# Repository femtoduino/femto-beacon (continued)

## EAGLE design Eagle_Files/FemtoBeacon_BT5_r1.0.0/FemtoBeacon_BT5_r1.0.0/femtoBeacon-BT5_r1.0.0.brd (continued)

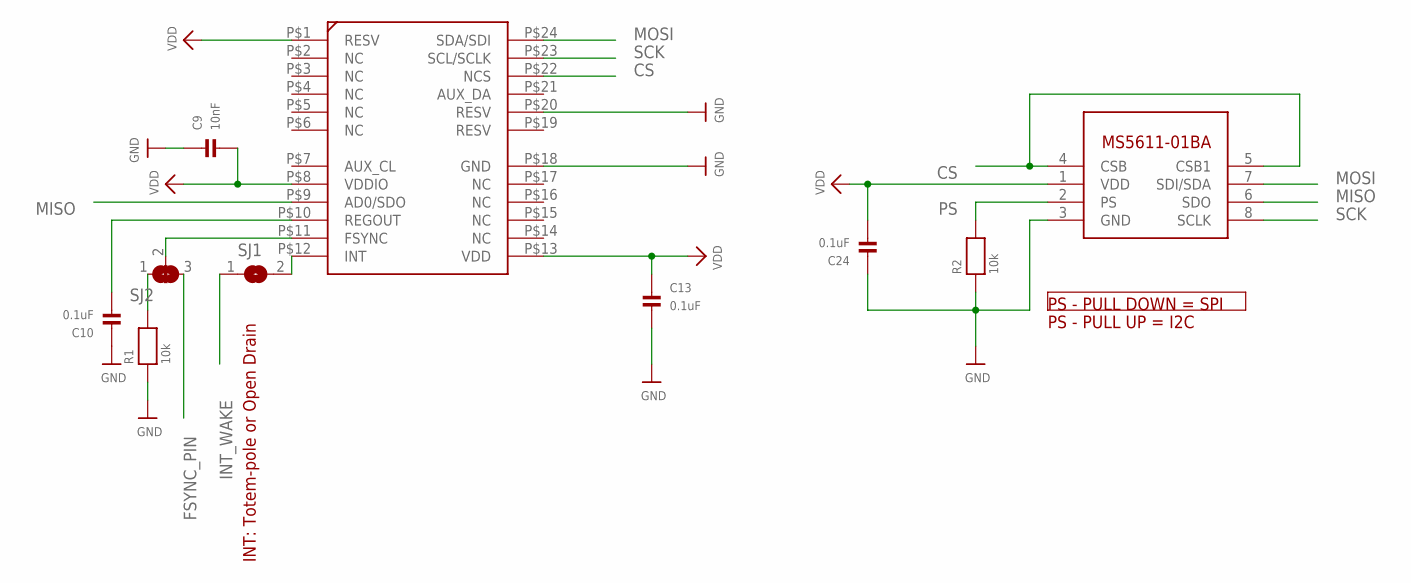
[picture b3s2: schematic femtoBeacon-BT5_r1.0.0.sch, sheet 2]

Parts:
BARO: MS5611-01BA03
C9: 10nF; _0402MP
C10, C13, C24: 0.1uF; _0402MP
IMU: MPU-9250; QFN_3X3MM
R1, R2: 10k; _0402MP
SJ1: SOLDERJUMPERCLOSED; SOLDERJUMPER_CLOSEDWIRE
SJ2: SOLDERJUMPER_2WAY; SOLDERJUMPER_2WAY_OPEN_NOPASTE

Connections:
CS: BARO.4 (CSB), BARO.5 (CSB1), IMU.P$22 (NCS); also elsewhere on the board
FSYNC: IMU.P$11 (FSYNC), SJ2.2
FSYNC_PIN: SJ2.3; also elsewhere on the board
GND: BARO.3 (GND), C9.1, C10.1, C13.2, C24.1, IMU.P$18 (GND), IMU.P$20 (RESV), R1.1, R2.1; also elsewhere on the board
INT: IMU.P$12 (INT), SJ1.2
INT_WAKE: SJ1.1; also elsewhere on the board
MISO: BARO.6 (SDO), IMU.P$9 (AD0/SDO); also elsewhere on the board
MOSI: BARO.7 (SDI/SDA), IMU.P$24 (SDA/SDI); also elsewhere on the board
unnamed: R1.2, SJ2.1
unnamed: C10.2, IMU.P$10 (REGOUT)
PS: BARO.2 (PS), R2.2
SCK: BARO.8 (SCLK), IMU.P$23 (SCL/SCLK); also elsewhere on the board
VDD: BARO.1 (VDD), C9.2, C13.1, C24.2, IMU.P$1 (RESV), IMU.P$8 (VDDIO), IMU.P$13 (VDD); also elsewhere on the board

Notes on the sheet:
INT: Totem-pole or Open Drain
PS - PULL DOWN = SPI
PS - PULL UP = I2C

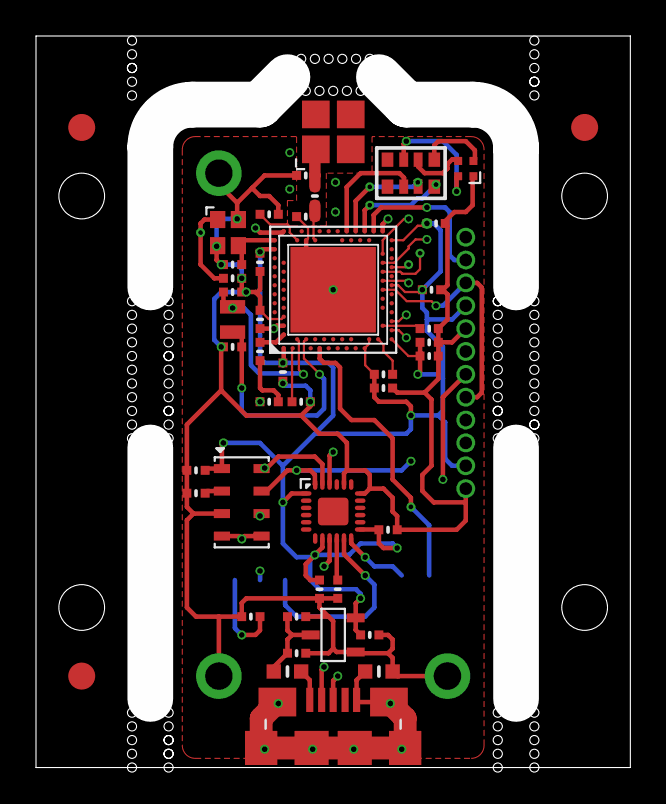
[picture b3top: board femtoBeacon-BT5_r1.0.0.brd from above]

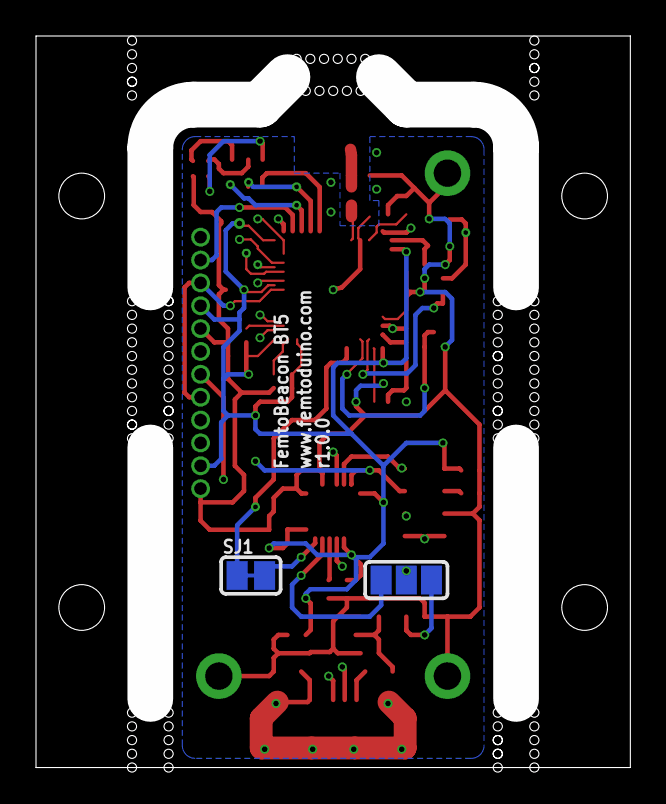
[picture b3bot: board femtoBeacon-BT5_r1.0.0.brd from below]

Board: 4 copper layers, 33.0 x 40.6 mm, 49 parts (2 on the bottom side), 40 nets.

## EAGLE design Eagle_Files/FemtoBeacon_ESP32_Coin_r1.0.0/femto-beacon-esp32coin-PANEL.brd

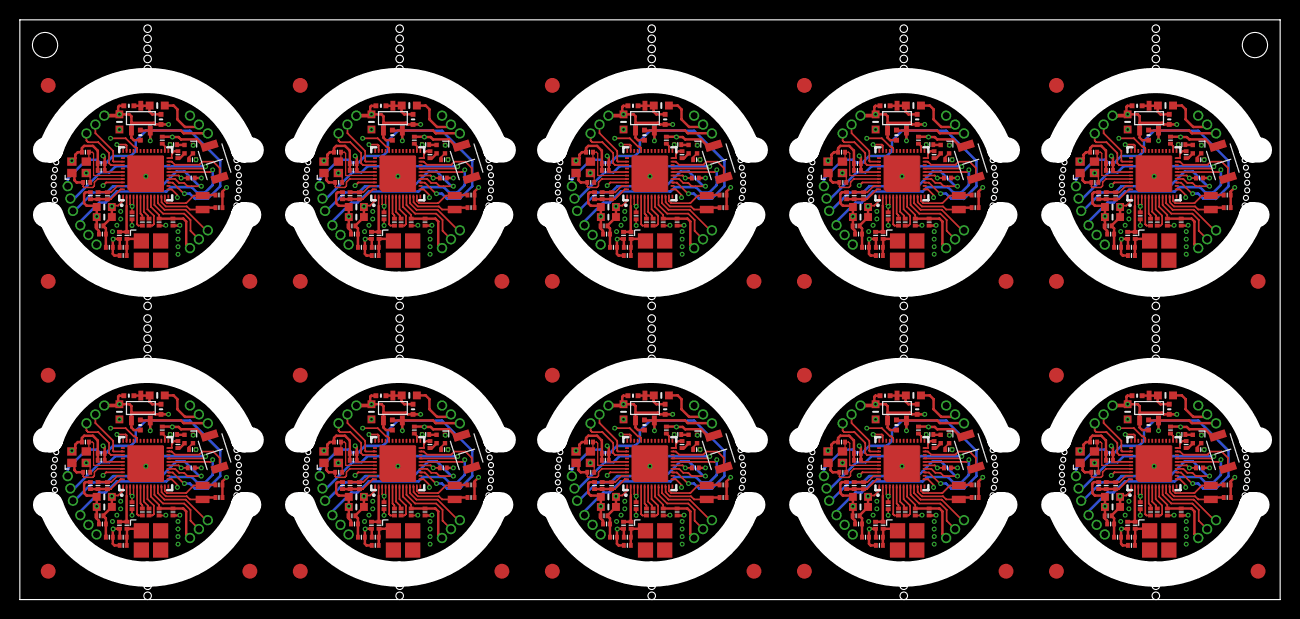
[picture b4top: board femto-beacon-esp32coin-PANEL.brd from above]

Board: 4 copper layers, 127.0 x 58.4 mm, 480 parts (0 on the bottom side), 340 nets.

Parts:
ANT1, ANT2, ANT3, ANT4, ANT5, ANT6, ANT7, ANT8, ANT9, ANT10: 0479480001
BOOT1, BOOT2, BOOT3, BOOT4, BOOT5, BOOT6, BOOT7, BOOT8, BOOT9, BOOT10: TACTILE_SWITCH_NO_GND_NO_BOSS; SIDE_ACT_NO_GND_NO_BOSS
C1, C15, C18, C26, C39, C42, C50, C63, C66, C74, C87, C90, C98, C111, C114, C122, C135, C138, C146, C159, C162, C170, C183, C186, C194, C207, C210, C218, C231, C234: 1uF; PART
C2, C3, C27, C28, C51, C52, C75, C76, C99, C100, C123, C124, C147, C148, C171, C172, C195, C196, C219, C220: 2.2uF; _0402MP
C4, C5, C29, C30, C53, C54, C77, C78, C101, C102, C125, C126, C149, C150, C173, C174, C197, C198, C221, C222: 10pF; PART
C6, C7, C25, C31, C49, C55, C73, C79, C97, C103, C121, C127, C145, C151, C169, C175, C193, C199, C217, C223: 270pF; PART
C8, C32, C56, C80, C104, C128, C152, C176, C200, C224: 6.8pF; PART
C9, C33, C57, C81, C105, C129, C153, C177, C201, C225: 2.4pF; PART
C10, C11, C34, C35, C58, C59, C82, C83, C106, C107, C130, C131, C154, C155, C178, C179, C202, C203, C226, C227: 10uF; _0603MP
C12, C13, C17, C19, C22, C36, C37, C41, C43, C46, C60, C61, C65, C67, C70, C84, C85, C89, C91, C94, C108, C109, C113, C115, C118, C132, C133, C137, C139, C142, C156, C157, C161, C163, C166, C180, C181, C185, C187, C190, C204, C205, C209, C211, C214, C228, C229, C233, C235, C238: 0.1uF; PART
C14, C38, C62, C86, C110, C134, C158, C182, C206, C230: 0.47uF; _0402MP
C16, C40, C64, C88, C112, C136, C160, C184, C208, C232: 100pF; PART
C20, C44, C68, C92, C116, C140, C164, C188, C212, C236: 10nF/6.3V(10%); PART
C21, C45, C69, C93, C117, C141, C165, C189, C213, C237: 3.3nF/6.3V(10%); PART
C23, C24, C47, C48, C71, C72, C95, C96, C119, C120, C143, C144, C167, C168, C191, C192, C215, C216, C239, C240: 4.1pF; PART
FB1, FB2, FB3, FB4, FB5, FB6, FB7, FB8, FB9, FB10, FB11, FB12, FB13, FB14, FB15, FB16, FB17, FB18, FB19, FB20: FERRITE; _0603MP
FID1, FID2, FID3, FID4, FID5, FID6, FID7, FID8, FID9, FID10, FID11, FID12, FID13, FID14, FID15, FID16, FID17, FID18, FID19, FID20, FID21, FID22, FID23, FID24, FID25, FID26, FID27, FID28, FID29, FID30: FIDUCIAL; FIDUCIAL_1MM
IC1, IC2, IC3, IC4, IC5, IC6, IC7, IC8, IC9, IC10: ESP32-QFN_5X5; ESP32-QFN48_5X5
L1, L2, L3, L4, L5, L6, L7, L8, L9, L10: 1.6nH; PART
LDO1, LDO2, LDO3, LDO4, LDO5, LDO6, LDO7, LDO8, LDO9, LDO10: MCP1700T-3302E/TT
PIN_EN, PIN_EN1, PIN_EN2, PIN_EN3, PIN_EN4, PIN_EN5, PIN_EN6, PIN_EN7, PIN_EN8, PIN_EN9: 1X3_ROUND
PIN_GPIO_A, PIN_GPIO_A1, PIN_GPIO_A2, PIN_GPIO_A3, PIN_GPIO_A4, PIN_GPIO_A5, PIN_GPIO_A6, PIN_GPIO_A7, PIN_GPIO_A8, PIN_GPIO_A9: 1X3_ROUND
PIN_GPIO_B, PIN_GPIO_B1, PIN_GPIO_B2, PIN_GPIO_B3, PIN_GPIO_B4, PIN_GPIO_B5, PIN_GPIO_B6, PIN_GPIO_B7, PIN_GPIO_B8, PIN_GPIO_B9: 1X3_ROUND
PIN_PWR, PIN_PWR1, PIN_PWR2, PIN_PWR3, PIN_PWR4, PIN_PWR5, PIN_PWR6, PIN_PWR7, PIN_PWR8, PIN_PWR9: 1X3_ROUND
PIN_UART, PIN_UART1, PIN_UART2, PIN_UART3, PIN_UART4, PIN_UART5, PIN_UART6, PIN_UART7, PIN_UART8, PIN_UART9: 1X3_ROUND
R1, R7, R13, R19, R25, R31, R37, R43, R49, R55: 20K(5%); PART
R2, R8, R14, R20, R26, R32, R38, R44, R50, R56: 10K; PART
R3, R4, R5, R9, R10, R11, R15, R16, R17, R21, R22, R23, R27, R28, R29, R33, R34, R35, R39, R40, R41, R45, R46, R47, R51, R52, R53, R57, R58, R59: 270; PART
R6, R12, R18, R24, R30, R36, R42, R48, R54, R60: DNP; PART
RGB1, RGB2, RGB3, RGB4, RGB5, RGB6, RGB7, RGB8, RGB9, RGB10: LRTB_R48G
XTAL1, XTAL3, XTAL5, XTAL7, XTAL9, XTAL11, XTAL13, XTAL15, XTAL17, XTAL19: 40MHz; FA-128
XTAL2, XTAL4, XTAL6, XTAL8, XTAL10, XTAL12, XTAL14, XTAL16, XTAL18, XTAL20: ABS06-107-32.768KHZ-T

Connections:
3.3V: C1.2, C2.2, C10.2, C11.2, C12.2, C13.2, C15.2, C16.2, C17.2, C19.2, IC1.1, IC1.3, IC1.4, IC1.19, IC1.37, IC1.43, IC1.46, LDO1.VOUT, PIN_GPIO_A.P$2, PIN_PWR.P$3, R2.1, RGB1.1
3.3V1: C26.2, C27.2, C34.2, C35.2, C36.2, C37.2, C39.2, C40.2, C41.2, C43.2, IC2.1, IC2.3, IC2.4, IC2.19, IC2.37, IC2.43, IC2.46, LDO2.VOUT, PIN_GPIO_A1.P$2, PIN_PWR1.P$3, R8.1, RGB2.1
3.3V2: C50.2, C51.2, C58.2, C59.2, C60.2, C61.2, C63.2, C64.2, C65.2, C67.2, IC3.1, IC3.3, IC3.4, IC3.19, IC3.37, IC3.43, IC3.46, LDO3.VOUT, PIN_GPIO_A2.P$2, PIN_PWR2.P$3, R14.1, RGB3.1
3.3V3: C74.2, C75.2, C82.2, C83.2, C84.2, C85.2, C87.2, C88.2, C89.2, C91.2, IC4.1, IC4.3, IC4.4, IC4.19, IC4.37, IC4.43, IC4.46, LDO4.VOUT, PIN_GPIO_A3.P$2, PIN_PWR3.P$3, R20.1, RGB4.1
3.3V4: C98.2, C99.2, C106.2, C107.2, C108.2, C109.2, C111.2, C112.2, C113.2, C115.2, IC5.1, IC5.3, IC5.4, IC5.19, IC5.37, IC5.43, IC5.46, LDO5.VOUT, PIN_GPIO_A4.P$2, PIN_PWR4.P$3, R26.1, RGB5.1
3.3V5: C122.2, C123.2, C130.2, C131.2, C132.2, C133.2, C135.2, C136.2, C137.2, C139.2, IC6.1, IC6.3, IC6.4, IC6.19, IC6.37, IC6.43, IC6.46, LDO6.VOUT, PIN_GPIO_A5.P$2, PIN_PWR5.P$3, R32.1, RGB6.1
3.3V6: C146.2, C147.2, C154.2, C155.2, C156.2, C157.2, C159.2, C160.2, C161.2, C163.2, IC7.1, IC7.3, IC7.4, IC7.19, IC7.37, IC7.43, IC7.46, LDO7.VOUT, PIN_GPIO_A6.P$2, PIN_PWR6.P$3, R38.1, RGB7.1
3.3V7: C170.2, C171.2, C178.2, C179.2, C180.2, C181.2, C183.2, C184.2, C185.2, C187.2, IC8.1, IC8.3, IC8.4, IC8.19, IC8.37, IC8.43, IC8.46, LDO8.VOUT, PIN_GPIO_A7.P$2, PIN_PWR7.P$3, R44.1, RGB8.1
3.3V8: C194.2, C195.2, C202.2, C203.2, C204.2, C205.2, C207.2, C208.2, C209.2, C211.2, IC9.1, IC9.3, IC9.4, IC9.19, IC9.37, IC9.43, IC9.46, LDO9.VOUT, PIN_GPIO_A8.P$2, PIN_PWR8.P$3, R50.1, RGB9.1
3.3V9: C218.2, C219.2, C226.2, C227.2, C228.2, C229.2, C231.2, C232.2, C233.2, C235.2, IC10.1, IC10.3, IC10.4, IC10.19, IC10.37, IC10.43, IC10.46, LDO10.VOUT, PIN_GPIO_A9.P$2, PIN_PWR9.P$3, R56.1, RGB10.1
32K_XN: C24.1, IC1.13, XTAL2.2
32K_XN1: C48.1, IC2.13, XTAL4.2
32K_XN2: C72.1, IC3.13, XTAL6.2
32K_XN3: C96.1, IC4.13, XTAL8.2
32K_XN4: C120.1, IC5.13, XTAL10.2
32K_XN5: C144.1, IC6.13, XTAL12.2
32K_XN6: C168.1, IC7.13, XTAL14.2
32K_XN7: C192.1, IC8.13, XTAL16.2
32K_XN8: C216.1, IC9.13, XTAL18.2
32K_XN9: C240.1, IC10.13, XTAL20.2
32K_XP: C23.2, IC1.12, XTAL2.1
32K_XP1: C47.2, IC2.12, XTAL4.1
32K_XP2: C71.2, IC3.12, XTAL6.1
32K_XP3: C95.2, IC4.12, XTAL8.1
32K_XP4: C119.2, IC5.12, XTAL10.1
32K_XP5: C143.2, IC6.12, XTAL12.1
32K_XP6: C167.2, IC7.12, XTAL14.1
32K_XP7: C191.2, IC8.12, XTAL16.1
32K_XP8: C215.2, IC9.12, XTAL18.1
32K_XP9: C239.2, IC10.12, XTAL20.1
ANT: C8.2, IC1.2, L2.2
ANT1: C32.2, IC2.2, L1.2
ANT2: C56.2, IC3.2, L3.2
ANT3: C80.2, IC4.2, L4.2
ANT4: C104.2, IC5.2, L5.2
ANT5: C128.2, IC6.2, L6.2
ANT6: C152.2, IC7.2, L7.2
ANT7: C176.2, IC8.2, L8.2
ANT8: C200.2, IC9.2, L9.2
ANT9: C224.2, IC10.2, L10.2
B: IC1.34, R3.2
B1: IC2.34, R9.2
B2: IC3.34, R15.2
B3: IC4.34, R21.2
B4: IC5.34, R27.2
B5: IC6.34, R33.2
B6: IC7.34, R39.2
B7: IC8.34, R45.2
B8: IC9.34, R51.2
B9: IC10.34, R57.2
BOOT: BOOT1.2, IC1.23
BOOT1: BOOT2.2, IC2.23
BOOT2: BOOT3.2, IC3.23
BOOT3: BOOT4.2, IC4.23
BOOT4: BOOT5.2, IC5.23
BOOT5: BOOT6.2, IC6.23
BOOT6: BOOT7.2, IC7.23
BOOT7: BOOT8.2, IC8.23
BOOT8: BOOT9.2, IC9.23
BOOT9: BOOT10.2, IC10.23
B_: R3.1, RGB1.4
B_1: R9.1, RGB2.4
B_2: R15.1, RGB3.4
B_3: R21.1, RGB4.4
B_4: R27.1, RGB5.4
B_5: R33.1, RGB6.4
B_6: R39.1, RGB7.4
B_7: R45.1, RGB8.4
B_8: R51.1, RGB9.4
B_9: R57.1, RGB10.4
G: IC1.24, R4.2
G1: IC2.24, R10.2
G2: IC3.24, R16.2
G3: IC4.24, R22.2
G4: IC5.24, R28.2
G5: IC6.24, R34.2
G6: IC7.24, R40.2
G7: IC8.24, R46.2
G8: IC9.24, R52.2
G9: IC10.24, R58.2
GND: BOOT1.1, C1.1, C2.1, C3.1, C4.1, C5.1, C9.1, C10.1, C11.1, C12.1, C13.1, C14.1, C15.1, C16.1, C17.1, C18.1, C19.1, C20.1, C22.1, C23.1, C24.2, FB1.2, IC1.49, L2.1, LDO1.GND, PIN_GPIO_A.P$3, PIN_UART.P$1, R6.1, XTAL1.2, XTAL1.4
GND1: BOOT2.1, C26.1, C27.1, C28.1, C29.1, C30.1, C33.1, C34.1, C35.1, C36.1, C37.1, C38.1, C39.1, C40.1, C41.1, C42.1, C43.1, C44.1, C46.1, C47.1, C48.2, FB3.2, IC2.49, L1.1, LDO2.GND, PIN_GPIO_A1.P$3, PIN_UART1.P$1, R12.1, XTAL3.2, XTAL3.4
GND2: BOOT3.1, C50.1, C51.1, C52.1, C53.1, C54.1, C57.1, C58.1, C59.1, C60.1, C61.1, C62.1, C63.1, C64.1, C65.1, C66.1, C67.1, C68.1, C70.1, C71.1, C72.2, FB5.2, IC3.49, L3.1, LDO3.GND, PIN_GPIO_A2.P$3, PIN_UART2.P$1, R18.1, XTAL5.2, XTAL5.4
GND3: BOOT4.1, C74.1, C75.1, C76.1, C77.1, C78.1, C81.1, C82.1, C83.1, C84.1, C85.1, C86.1, C87.1, C88.1, C89.1, C90.1, C91.1, C92.1, C94.1, C95.1, C96.2, FB7.2, IC4.49, L4.1, LDO4.GND, PIN_GPIO_A3.P$3, PIN_UART3.P$1, R24.1, XTAL7.2, XTAL7.4
GND4: BOOT5.1, C98.1, C99.1, C100.1, C101.1, C102.1, C105.1, C106.1, C107.1, C108.1, C109.1, C110.1, C111.1, C112.1, C113.1, C114.1, C115.1, C116.1, C118.1, C119.1, C120.2, FB9.2, IC5.49, L5.1, LDO5.GND, PIN_GPIO_A4.P$3, PIN_UART4.P$1, R30.1, XTAL9.2, XTAL9.4
GND5: BOOT6.1, C122.1, C123.1, C124.1, C125.1, C126.1, C129.1, C130.1, C131.1, C132.1, C133.1, C134.1, C135.1, C136.1, C137.1, C138.1, C139.1, C140.1, C142.1, C143.1, C144.2, FB11.2, IC6.49, L6.1, LDO6.GND, PIN_GPIO_A5.P$3, PIN_UART5.P$1, R36.1, XTAL11.2, XTAL11.4
GND6: BOOT7.1, C146.1, C147.1, C148.1, C149.1, C150.1, C153.1, C154.1, C155.1, C156.1, C157.1, C158.1, C159.1, C160.1, C161.1, C162.1, C163.1, C164.1, C166.1, C167.1, C168.2, FB13.2, IC7.49, L7.1, LDO7.GND, PIN_GPIO_A6.P$3, PIN_UART6.P$1, R42.1, XTAL13.2, XTAL13.4
GND7: BOOT8.1, C170.1, C171.1, C172.1, C173.1, C174.1, C177.1, C178.1, C179.1, C180.1, C181.1, C182.1, C183.1, C184.1, C185.1, C186.1, C187.1, C188.1, C190.1, C191.1, C192.2, FB15.2, IC8.49, L8.1, LDO8.GND, PIN_GPIO_A7.P$3, PIN_UART7.P$1, R48.1, XTAL15.2, XTAL15.4
GND8: BOOT9.1, C194.1, C195.1, C196.1, C197.1, C198.1, C201.1, C202.1, C203.1, C204.1, C205.1, C206.1, C207.1, C208.1, C209.1, C210.1, C211.1, C212.1, C214.1, C215.1, C216.2, FB17.2, IC9.49, L9.1, LDO9.GND, PIN_GPIO_A8.P$3, PIN_UART8.P$1, R54.1, XTAL17.2, XTAL17.4
GND9: BOOT10.1, C218.1, C219.1, C220.1, C221.1, C222.1, C225.1, C226.1, C227.1, C228.1, C229.1, C230.1, C231.1, C232.1, C233.1, C234.1, C235.1, C236.1, C238.1, C239.1, C240.2, FB19.2, IC10.49, L10.1, LDO10.GND, PIN_GPIO_A9.P$3, PIN_UART9.P$1, R60.1, XTAL19.2, XTAL19.4
GND_PIN: FB1.1, PIN_PWR.P$1
GND_PIN1: FB3.1, PIN_PWR1.P$1
GND_PIN2: FB5.1, PIN_PWR2.P$1
GND_PIN3: FB7.1, PIN_PWR3.P$1
GND_PIN4: FB9.1, PIN_PWR4.P$1
GND_PIN5: FB11.1, PIN_PWR5.P$1
GND_PIN6: FB13.1, PIN_PWR6.P$1
GND_PIN7: FB15.1, PIN_PWR7.P$1
GND_PIN8: FB17.1, PIN_PWR8.P$1
GND_PIN9: FB19.1, PIN_PWR9.P$1
G_: R4.1, RGB1.3
G_1: R10.1, RGB2.3
G_2: R16.1, RGB3.3
G_3: R22.1, RGB4.3
G_4: R28.1, RGB5.3
G_5: R34.1, RGB6.3
G_6: R40.1, RGB7.3
G_7: R46.1, RGB8.3
G_8: R52.1, RGB9.3
G_9: R58.1, RGB10.3
IO1: IC2.10, PIN_EN1.P$2
IO2: IC2.11, PIN_EN1.P$1
IO5: IC3.10, PIN_EN2.P$2
IO6: IC3.11, PIN_EN2.P$1
IO9: IC4.10, PIN_EN3.P$2
IO10: IC4.11, PIN_EN3.P$1
IO13: IC5.10, PIN_EN4.P$2
IO14: IC5.11, PIN_EN4.P$1
IO17: IC6.10, PIN_EN5.P$2
IO18: IC6.11, PIN_EN5.P$1
IO21: IC7.10, PIN_EN6.P$2
IO22: IC7.11, PIN_EN6.P$1
IO26: IC8.10, PIN_EN7.P$2
IO28: IC8.11, PIN_EN7.P$1
IO31: IC9.10, PIN_EN8.P$2
IO32: IC9.11, PIN_EN8.P$1
IO34: IC1.10, PIN_EN.P$2
IO35: IC1.11, PIN_EN.P$1
IO37: IC10.10, PIN_EN9.P$2
IO38: IC10.11, PIN_EN9.P$1
MTCK: IC1.20, PIN_GPIO_A.P$1
MTCK1: IC2.20, PIN_GPIO_A1.P$1
MTCK2: IC3.20, PIN_GPIO_A2.P$1
MTCK3: IC4.20, PIN_GPIO_A3.P$1
MTCK4: IC5.20, PIN_GPIO_A4.P$1
MTCK5: IC6.20, PIN_GPIO_A5.P$1
MTCK6: IC7.20, PIN_GPIO_A6.P$1
MTCK7: IC8.20, PIN_GPIO_A7.P$1
MTCK8: IC9.20, PIN_GPIO_A8.P$1
MTCK9: IC10.20, PIN_GPIO_A9.P$1
MTDI: IC1.18, PIN_GPIO_B.P$3
MTDI1: IC2.18, PIN_GPIO_B1.P$3
MTDI2: IC3.18, PIN_GPIO_B2.P$3
MTDI3: IC4.18, PIN_GPIO_B3.P$3
MTDI4: IC5.18, PIN_GPIO_B4.P$3
MTDI5: IC6.18, PIN_GPIO_B5.P$3
MTDI6: IC7.18, PIN_GPIO_B6.P$3
MTDI7: IC8.18, PIN_GPIO_B7.P$3
MTDI8: IC9.18, PIN_GPIO_B8.P$3
MTDI9: IC10.18, PIN_GPIO_B9.P$3
MTDO: IC1.21, PIN_GPIO_B.P$2
MTDO1: IC2.21, PIN_GPIO_B1.P$2
MTDO2: IC3.21, PIN_GPIO_B2.P$2
MTDO3: IC4.21, PIN_GPIO_B3.P$2
MTDO4: IC5.21, PIN_GPIO_B4.P$2
MTDO5: IC6.21, PIN_GPIO_B5.P$2
MTDO6: IC7.21, PIN_GPIO_B6.P$2
MTDO7: IC8.21, PIN_GPIO_B7.P$2
MTDO8: IC9.21, PIN_GPIO_B8.P$2
MTDO9: IC10.21, PIN_GPIO_B9.P$2
MTMS: IC1.17, PIN_GPIO_B.P$1
MTMS1: IC2.17, PIN_GPIO_B1.P$1
MTMS2: IC3.17, PIN_GPIO_B2.P$1
MTMS3: IC4.17, PIN_GPIO_B3.P$1
MTMS4: IC5.17, PIN_GPIO_B4.P$1
MTMS5: IC6.17, PIN_GPIO_B5.P$1
MTMS6: IC7.17, PIN_GPIO_B6.P$1
MTMS7: IC8.17, PIN_GPIO_B7.P$1
MTMS8: IC9.17, PIN_GPIO_B8.P$1
MTMS9: IC10.17, PIN_GPIO_B9.P$1
unnamed: C6.1, IC1.5
unnamed: C6.2, IC1.6
unnamed: C7.2, IC1.8
unnamed: C7.1, IC1.7
unnamed: C25.2, IC2.6
unnamed: ANT1.ANT, C8.1, C9.2, R6.2
unnamed: C21.2, IC1.47, R1.1
unnamed: C20.2, C21.1, IC1.48, R1.2
unnamed: C31.2, IC2.8
unnamed: C31.1, IC2.7
unnamed: ANT2.ANT, C32.1, C33.2, R12.2
unnamed: C25.1, IC2.5
unnamed: C45.2, IC2.47, R7.1
unnamed: C44.2, C45.1, IC2.48, R7.2
unnamed: C49.2, IC3.6
unnamed: C55.2, IC3.8
unnamed: C55.1, IC3.7
unnamed: ANT3.ANT, C56.1, C57.2, R18.2
unnamed: C49.1, IC3.5
unnamed: C69.2, IC3.47, R13.1
unnamed: C68.2, C69.1, IC3.48, R13.2
unnamed: C73.2, IC4.6
unnamed: C79.2, IC4.8
unnamed: C79.1, IC4.7
unnamed: ANT4.ANT, C80.1, C81.2, R24.2
unnamed: C73.1, IC4.5
unnamed: C93.2, IC4.47, R19.1
unnamed: C92.2, C93.1, IC4.48, R19.2
unnamed: C97.2, IC5.6
unnamed: C103.2, IC5.8
unnamed: C103.1, IC5.7
unnamed: ANT5.ANT, C104.1, C105.2, R30.2
unnamed: C97.1, IC5.5
unnamed: C117.2, IC5.47, R25.1
unnamed: C116.2, C117.1, IC5.48, R25.2
unnamed: C121.2, IC6.6
unnamed: C127.2, IC6.8
unnamed: C127.1, IC6.7
unnamed: ANT6.ANT, C128.1, C129.2, R36.2
unnamed: C121.1, IC6.5
unnamed: C141.2, IC6.47, R31.1
unnamed: C140.2, C141.1, IC6.48, R31.2
unnamed: C145.2, IC7.6
unnamed: C151.2, IC7.8
unnamed: C151.1, IC7.7
unnamed: ANT7.ANT, C152.1, C153.2, R42.2
unnamed: C145.1, IC7.5
unnamed: C165.2, IC7.47, R37.1
unnamed: C164.2, C165.1, IC7.48, R37.2
unnamed: C169.2, IC8.6
unnamed: C175.2, IC8.8
unnamed: C175.1, IC8.7
unnamed: ANT8.ANT, C176.1, C177.2, R48.2
unnamed: C169.1, IC8.5
unnamed: C189.2, IC8.47, R43.1
unnamed: C188.2, C189.1, IC8.48, R43.2
unnamed: C193.2, IC9.6
unnamed: C199.2, IC9.8
unnamed: C199.1, IC9.7
unnamed: ANT9.ANT, C200.1, C201.2, R54.2
unnamed: C193.1, IC9.5
unnamed: C213.2, IC9.47, R49.1
unnamed: C212.2, C213.1, IC9.48, R49.2
unnamed: C217.2, IC10.6
unnamed: C223.2, IC10.8
unnamed: C223.1, IC10.7
unnamed: ANT10.ANT, C224.1, C225.2, R60.2
unnamed: C217.1, IC10.5
unnamed: C237.2, IC10.47, R55.1
unnamed: C236.2, C237.1, IC10.48, R55.2
R: IC1.15, R5.2
R1: IC2.15, R11.2
R2: IC3.15, R17.2
R3: IC4.15, R23.2
R4: IC5.15, R29.2
R5: IC6.15, R35.2
R6: IC7.15, R41.2
R7: IC8.15, R47.2
R8: IC9.15, R53.2
R9: IC10.15, R59.2
RESET: C22.2, IC1.9, PIN_EN.P$3, R2.2
RESET1: C46.2, IC2.9, PIN_EN1.P$3, R8.2
RESET2: C70.2, IC3.9, PIN_EN2.P$3, R14.2
RESET3: C94.2, IC4.9, PIN_EN3.P$3, R20.2
RESET4: C118.2, IC5.9, PIN_EN4.P$3, R26.2
RESET5: C142.2, IC6.9, PIN_EN5.P$3, R32.2
RESET6: C166.2, IC7.9, PIN_EN6.P$3, R38.2
RESET7: C190.2, IC8.9, PIN_EN7.P$3, R44.2
RESET8: C214.2, IC9.9, PIN_EN8.P$3, R50.2
RESET9: C238.2, IC10.9, PIN_EN9.P$3, R56.2
RXD: IC1.40, PIN_UART.P$2
RXD1: IC2.40, PIN_UART1.P$2
RXD2: IC3.40, PIN_UART2.P$2
RXD3: IC4.40, PIN_UART3.P$2
RXD4: IC5.40, PIN_UART4.P$2
RXD5: IC6.40, PIN_UART5.P$2
RXD6: IC7.40, PIN_UART6.P$2
RXD7: IC8.40, PIN_UART7.P$2
RXD8: IC9.40, PIN_UART8.P$2
RXD9: IC10.40, PIN_UART9.P$2
R_: R5.1, RGB1.2
R_1: R11.1, RGB2.2
R_2: R17.1, RGB3.2
R_3: R23.1, RGB4.2
R_4: R29.1, RGB5.2
R_5: R35.1, RGB6.2
R_6: R41.1, RGB7.2
R_7: R47.1, RGB8.2
R_8: R53.1, RGB9.2
R_9: R59.1, RGB10.2
TXD: IC1.41, PIN_UART.P$3
TXD1: IC2.41, PIN_UART1.P$3
TXD2: IC3.41, PIN_UART2.P$3
TXD3: IC4.41, PIN_UART3.P$3
TXD4: IC5.41, PIN_UART4.P$3
TXD5: IC6.41, PIN_UART5.P$3
TXD6: IC7.41, PIN_UART6.P$3
TXD7: IC8.41, PIN_UART7.P$3
TXD8: IC9.41, PIN_UART8.P$3
TXD9: IC10.41, PIN_UART9.P$3
VDD_SDIO: C18.2, IC1.26
VDD_SDIO1: C42.2, IC2.26
VDD_SDIO2: C66.2, IC3.26
VDD_SDIO3: C90.2, IC4.26
VDD_SDIO4: C114.2, IC5.26
VDD_SDIO5: C138.2, IC6.26
VDD_SDIO6: C162.2, IC7.26
VDD_SDIO7: C186.2, IC8.26
VDD_SDIO8: C210.2, IC9.26
VDD_SDIO9: C234.2, IC10.26
VIN: C3.2, C14.2, FB2.1, LDO1.VIN
VIN1: C28.2, C38.2, FB4.1, LDO2.VIN
VIN2: C52.2, C62.2, FB6.1, LDO3.VIN
VIN3: C76.2, C86.2, FB8.1, LDO4.VIN
VIN4: C100.2, C110.2, FB10.1, LDO5.VIN
VIN5: C124.2, C134.2, FB12.1, LDO6.VIN
VIN6: C148.2, C158.2, FB14.1, LDO7.VIN
VIN7: C172.2, C182.2, FB16.1, LDO8.VIN
VIN8: C196.2, C206.2, FB18.1, LDO9.VIN
VIN9: C220.2, C230.2, FB20.1, LDO10.VIN
VIN_PIN: FB2.2, PIN_PWR.P$2
VIN_PIN1: FB4.2, PIN_PWR1.P$2
VIN_PIN2: FB6.2, PIN_PWR2.P$2
VIN_PIN3: FB8.2, PIN_PWR3.P$2
VIN_PIN4: FB10.2, PIN_PWR4.P$2
VIN_PIN5: FB12.2, PIN_PWR5.P$2
VIN_PIN6: FB14.2, PIN_PWR6.P$2
VIN_PIN7: FB16.2, PIN_PWR7.P$2
VIN_PIN8: FB18.2, PIN_PWR8.P$2
VIN_PIN9: FB20.2, PIN_PWR9.P$2
XIN: C4.2, IC1.45, XTAL1.1
XIN1: C29.2, IC2.45, XTAL3.1
XIN2: C53.2, IC3.45, XTAL5.1
XIN3: C77.2, IC4.45, XTAL7.1
XIN4: C101.2, IC5.45, XTAL9.1
XIN5: C125.2, IC6.45, XTAL11.1
XIN6: C149.2, IC7.45, XTAL13.1
XIN7: C173.2, IC8.45, XTAL15.1
XIN8: C197.2, IC9.45, XTAL17.1
XIN9: C221.2, IC10.45, XTAL19.1
XOUT: C5.2, IC1.44, XTAL1.3
XOUT1: C30.2, IC2.44, XTAL3.3
XOUT2: C54.2, IC3.44, XTAL5.3
XOUT3: C78.2, IC4.44, XTAL7.3
XOUT4: C102.2, IC5.44, XTAL9.3
XOUT5: C126.2, IC6.44, XTAL11.3
XOUT6: C150.2, IC7.44, XTAL13.3
XOUT7: C174.2, IC8.44, XTAL15.3
XOUT8: C198.2, IC9.44, XTAL17.3
XOUT9: C222.2, IC10.44, XTAL19.3

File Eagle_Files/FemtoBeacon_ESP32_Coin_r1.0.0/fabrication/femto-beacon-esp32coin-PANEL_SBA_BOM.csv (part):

##########################################################################,,,,,
       Name: Placement Bill of Materials Generator,,,,,
,,,,,
    Version: 4 (2-sided, top),,,,
         By: Small Batch Assembly,,,,,
        URL: www.smallbatchassembly.com,,,,,
 SourceFile: femto-beacon-esp32coin-PANEL.brd,,,,,
   DateTime: 4/24/19 7:05 PM,,,,,
      Units: inches,,,,,
##########################################################################,,,,,
REF,PACKAGE,VALUE,X,Y,ROTATION
ANT1   ,479480001,479480001,0.52,0.235,0
ANT2   ,479480001,479480001,0.52,1.235,0
ANT3   ,479480001,479480001,1.47,0.235,0
ANT4   ,479480001,479480001,1.47,1.235,0
ANT5   ,479480001,479480001,2.42,0.235,0
ANT6   ,479480001,479480001,2.42,1.235,0
ANT7   ,479480001,479480001,3.37,0.235,0
ANT8   ,479480001,479480001,3.37,1.235,0
ANT9   ,479480001,479480001,4.32,0.235,0
ANT10   ,479480001,479480001,4.32,1.235,0
BOOT1   , SIDE_ACT_NO_GND_NO_BOSS            , TACTILE_SWITCH_NO_GND_NO_BOSS     ,0.7725,0.5868,287.5
BOOT2   , SIDE_ACT_NO_GND_NO_BOSS            , TACTILE_SWITCH_NO_GND_NO_BOSS     ,0.7725,1.5868,287.5
BOOT3   , SIDE_ACT_NO_GND_NO_BOSS            , TACTILE_SWITCH_NO_GND_NO_BOSS     ,1.7225,0.5868,287.5
BOOT4   , SIDE_ACT_NO_GND_NO_BOSS            , TACTILE_SWITCH_NO_GND_NO_BOSS     ,1.7225,1.5868,287.5
BOOT5   , SIDE_ACT_NO_GND_NO_BOSS            , TACTILE_SWITCH_NO_GND_NO_BOSS     ,2.6725,0.5868,287.5
BOOT6   , SIDE_ACT_NO_GND_NO_BOSS            , TACTILE_SWITCH_NO_GND_NO_BOSS     ,2.6725,1.5868,287.5
BOOT7   , SIDE_ACT_NO_GND_NO_BOSS            , TACTILE_SWITCH_NO_GND_NO_BOSS     ,3.6225,0.5868,287.5
BOOT8   , SIDE_ACT_NO_GND_NO_BOSS            , TACTILE_SWITCH_NO_GND_NO_BOSS     ,3.6225,1.5868,287.5
BOOT9   , SIDE_ACT_NO_GND_NO_BOSS            , TACTILE_SWITCH_NO_GND_NO_BOSS     ,4.5725,0.5868,287.5
BOOT10   , SIDE_ACT_NO_GND_NO_BOSS            , TACTILE_SWITCH_NO_GND_NO_BOSS     ,4.5725,1.5868,287.5
C1   , PART            , 1uF     ,0.3175,0.3325,0
C2   , _0402MP            , 2.2uF     ,0.478,0.6925,90
C3   , _0402MP            , 2.2uF     ,0.4325,0.8089,0
C4   , PART            , 10pF     ,0.265,0.505,180
C5   , PART            , 10pF     ,0.26,0.625,0
C6   , PART            , 270pF     ,0.486,0.3475,90
C7   , PART            , 270pF     ,0.5125,0.3475,270
C8   , PART            , 6.8pF     ,0.425,0.295,90
C9   , PART            , 2.4pF     ,0.41,0.2475,0
C10   , _0603MP            , 10uF     ,0.335,0.4075,0
C11   , _0603MP            , 10uF     ,0.335,0.3675,0
C12   , PART            , 0.1uF     ,0.3275,0.3,0
C13   , PART            , 0.1uF     ,0.355,0.2475,180
C14   , _0402MP            , 0.47uF     ,0.56,0.755,90
C15   , PART            , 1uF     ,0.3227,0.5525,0
C16   , PART            , 100pF     ,0.3227,0.58,0
C17   , PART            , 0.1uF     ,0.445,0.3725,90
C18   , PART            , 1uF     ,0.565,0.6725,270
C19   , PART            , 0.1uF     ,0.68,0.5225,180
C20   , PART            , 10nF/6.3V(10%)     ,0.28,0.4522,270
C21   , PART            , 3.3nF/6.3V(10%)     ,0.3475,0.452,90
C22   , PART            , 0.1uF     ,0.5525,0.3475,90
C23   , PART            , 4.1pF     ,0.79,0.405,180
C24   , PART            , 4.1pF     ,0.79,0.455,0
C25   , PART            , 270pF     ,0.486,1.3475,90
C26   , PART            , 1uF     ,0.3175,1.3325,0
C27   , _0402MP            , 2.2uF     ,0.478,1.6925,90
C28   , _0402MP            , 2.2uF     ,0.4325,1.8089,0
C29   , PART            , 10pF     ,0.265,1.505,180
C30   , PART            , 10pF     ,0.26,1.625,0
C31   , PART            , 270pF     ,0.5125,1.3475,270
C32   , PART            , 6.8pF     ,0.425,1.295,90
C33   , PART            , 2.4pF     ,0.41,1.2475,0
C34   , _0603MP            , 10uF     ,0.335,1.4075,0
C35   , _0603MP            , 10uF     ,0.335,1.3675,0
C36   , PART            , 0.1uF     ,0.3275,1.3,0
C37   , PART            , 0.1uF     ,0.355,1.2475,180
C38   , _0402MP            , 0.47uF     ,0.56,1.755,90
C39   , PART            , 1uF     ,0.3227,1.5525,0
C40   , PART            , 100pF     ,0.3227,1.58,0
C41   , PART            , 0.1uF     ,0.445,1.3725,90
C42   , PART            , 1uF     ,0.565,1.6725,270
C43   , PART            , 0.1uF     ,0.68,1.5225,180
C44   , PART            , 10nF/6.3V(10%)     ,0.28,1.4523,270
C45   , PART            , 3.3nF/6.3V(10%)     ,0.3475,1.452,90
C46   , PART            , 0.1uF     ,0.5525,1.3475,90
C47   , PART            , 4.1pF     ,0.79,1.405,180
C48   , PART            , 4.1pF     ,0.79,1.455,0
C49   , PART            , 270pF     ,1.436,0.3475,90
C50   , PART            , 1uF     ,1.2675,0.3325,0
C51   , _0402MP            , 2.2uF     ,1.428,0.6925,90
C52   , _0402MP            , 2.2uF     ,1.3825,0.8089,0
C53   , PART            , 10pF     ,1.215,0.505,180
C54   , PART            , 10pF     ,1.21,0.625,0
C55   , PART            , 270pF     ,1.4625,0.3475,270
C56   , PART            , 6.8pF     ,1.375,0.295,90
C57   , PART            , 2.4pF     ,1.36,0.2475,0
C58   , _0603MP            , 10uF     ,1.285,0.4075,0
C59   , _0603MP            , 10uF     ,1.285,0.3675,0
C60   , PART            , 0.1uF     ,1.2775,0.3,0
C61   , PART            , 0.1uF     ,1.305,0.2475,180
C62   , _0402MP            , 0.47uF     ,1.51,0.755,90
C63   , PART            , 1uF     ,1.2728,0.5525,0
C64   , PART            , 100pF     ,1.2728,0.58,0
C65   , PART            , 0.1uF     ,1.395,0.3725,90
C66   , PART            , 1uF     ,1.515,0.6725,270
C67   , PART            , 0.1uF     ,1.63,0.5225,180
C68   , PART            , 10nF/6.3V(10%)     ,1.23,0.4522,270
C69   , PART            , 3.3nF/6.3V(10%)     ,1.2975,0.452,90
C70   , PART            , 0.1uF     ,1.5025,0.3475,90
C71   , PART            , 4.1pF     ,1.74,0.405,180
C72   , PART            , 4.1pF     ,1.74,0.455,0
C73   , PART            , 270pF     ,1.436,1.3475,90
C74   , PART            , 1uF     ,1.2675,1.3325,0
C75   , _0402MP            , 2.2uF     ,1.428,1.6925,90
C76   , _0402MP            , 2.2uF     ,1.3825,1.8089,0
C77   , PART            , 10pF     ,1.215,1.505,180
C78   , PART            , 10pF     ,1.21,1.625,0
C79   , PART            , 270pF     ,1.4625,1.3475,270
C80   , PART            , 6.8pF     ,1.375,1.295,90
C81   , PART            , 2.4pF     ,1.36,1.2475,0
C82   , _0603MP            , 10uF     ,1.285,1.4075,0
C83   , _0603MP            , 10uF     ,1.285,1.3675,0
C84   , PART            , 0.1uF     ,1.2775,1.3,0
C85   , PART            , 0.1uF     ,1.305,1.2475,180
C86   , _0402MP            , 0.47uF     ,1.51,1.755,90
C87   , PART            , 1uF     ,1.2728,1.5525,0
C88   , PART            , 100pF     ,1.2728,1.58,0
C89   , PART            , 0.1uF     ,1.395,1.3725,90
C90   , PART            , 1uF     ,1.515,1.6725,270
C91   , PART            , 0.1uF     ,1.63,1.5225,180
C92   , PART            , 10nF/6.3V(10%)     ,1.23,1.4523,270
C93   , PART            , 3.3nF/6.3V(10%)     ,1.2975,1.452,90
C94   , PART            , 0.1uF     ,1.5025,1.3475,90
C95   , PART            , 4.1pF     ,1.74,1.405,180
C96   , PART            , 4.1pF     ,1.74,1.455,0
C97   , PART            , 270pF     ,2.386,0.3475,90
C98   , PART            , 1uF     ,2.2175,0.3325,0
C99   , _0402MP            , 2.2uF     ,2.378,0.6925,90
C100   , _0402MP            , 2.2uF     ,2.3325,0.8089,0
C101   , PART            , 10pF     ,2.165,0.505,180
C102   , PART            , 10pF     ,2.16,0.625,0
C103   , PART            , 270pF     ,2.4125,0.3475,270
C104   , PART            , 6.8pF     ,2.325,0.295,90
C105   , PART            , 2.4pF     ,2.31,0.2475,0
C106   , _0603MP            , 10uF     ,2.235,0.4075,0
C107   , _0603MP            , 10uF     ,2.235,0.3675,0
C108   , PART            , 0.1uF     ,2.2275,0.3,0
C109   , PART            , 0.1uF     ,2.255,0.2475,180
C110   , _0402MP            , 0.47uF     ,2.46,0.755,90
C111   , PART            , 1uF     ,2.2228,0.5525,0
C112   , PART            , 100pF     ,2.2228,0.58,0
C113   , PART            , 0.1uF     ,2.345,0.3725,90
C114   , PART            , 1uF     ,2.465,0.6725,270
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
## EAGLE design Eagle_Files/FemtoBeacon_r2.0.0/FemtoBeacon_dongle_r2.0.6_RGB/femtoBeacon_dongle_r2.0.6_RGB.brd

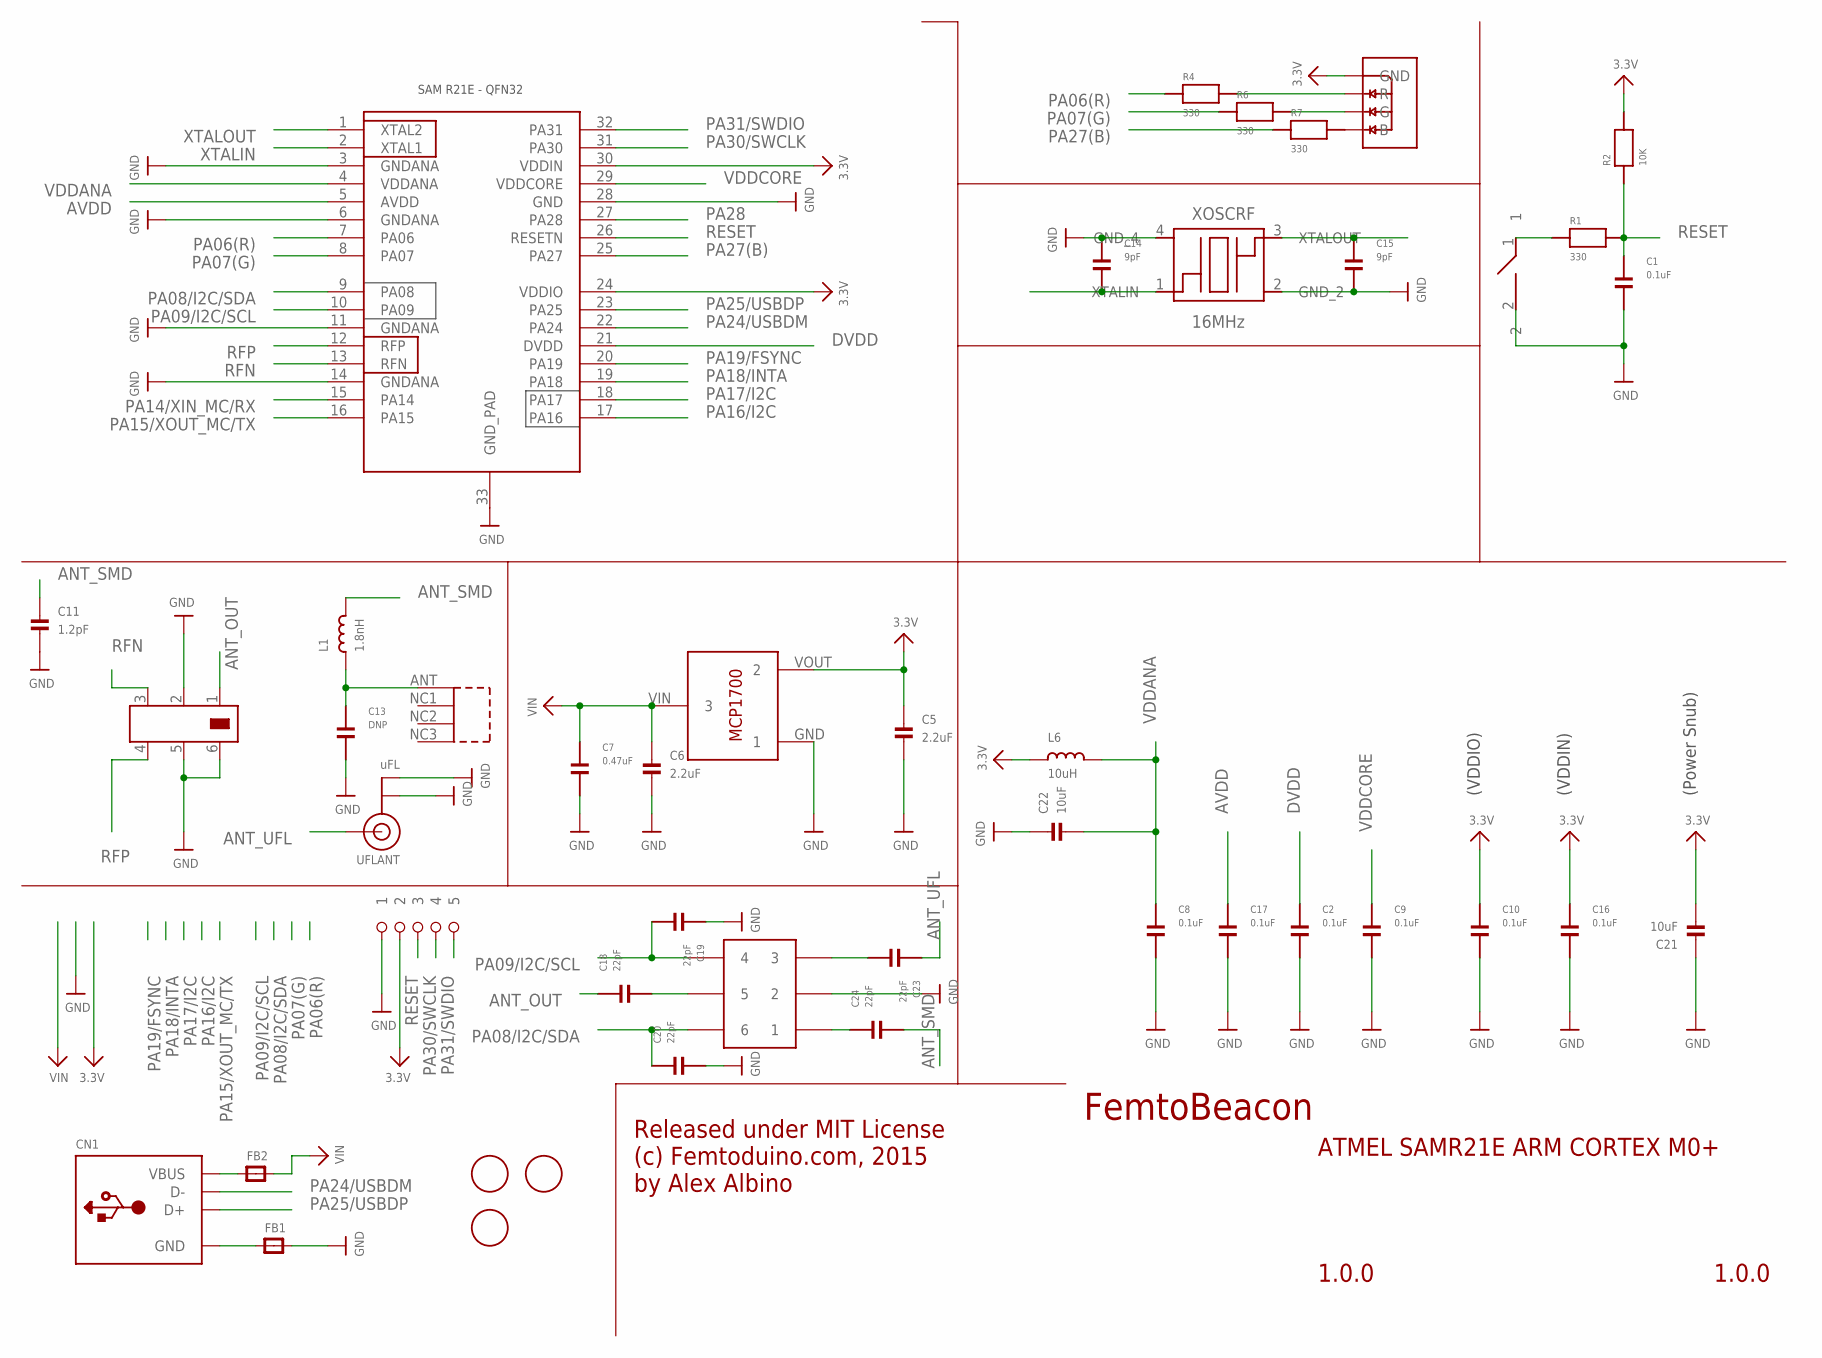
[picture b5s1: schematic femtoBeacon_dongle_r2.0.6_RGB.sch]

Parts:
ASWITCH: AS222-92LF
BTN: DNP; SPST_SMD
C1, C2, C8, C9, C10, C16, C17: 0.1uF; PART
C5, C6: 2.2uF; _0402MP
C7: 0.47uF; PART
C11: 1.2pF; _0402MP
C13: DNP; PART
C14, C15: 9pF; PART
C18, C19, C20, C23, C24: 22pF; PART
C21, C22: 10uF; _0402MP
CN1: USB_TYPEA; USB_A-SMT
FB1, FB2: FERRITE_0603MP; _0603MP
FID1, FID2, FID3: FIDUCIAL; FIDUCIAL_1MM
L1: 1.8nH; _0603MP
L6: 10uH; _0603MP
LDO_VREG: MCP1700T-3302E/TT
R1, R4, R6, R7: 330; PART
R2: 10K; PART
RGBLED: LRTB_R48G
U$1: 1X5_ROUND
U$6: 0479480001
U$12: JOHANSON_2450BM15A0015E; 0805_BALUN
U$76: ATSAMR21E18A-MUT; QFN32
UFLANT: uFL; U.FL
XOSCRF: 16MHz; TSX-3225

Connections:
3.3V: C5.1, C10.1, C16.1, C21.2, L6.1, LDO_VREG.VOUT (2), R2.2, RGBLED.1 (GND), U$1.P$2 (2), U$76.24 (VDDIO), U$76.30 (VDDIN)
ANT_LINE: C13.1, L1.1, U$6.ANT (1)
ANT_OUT: C18.1, U$12.1
ANT_SMD: C11.1, C24.2, L1.2
ANT_UFL: C23.1, UFLANT.3 (SIGNAL)
AVDD: C17.1, U$76.5 (AVDD)
DVDD: C2.1, U$76.21 (DVDD)
GND: ASWITCH.PIN2 (2), BTN.2, C1.2, C2.2, C5.2, C6.2, C7.2, C8.2, C9.2, C10.2, C11.2, C13.2, C14.1, C15.2, C16.2, C17.2, C19.1, C20.2, C21.1, C22.1, FB1.2, LDO_VREG.GND (1), U$1.P$1 (1), U$12.2, U$12.5, U$12.6, U$76.3 (GNDANA), U$76.6 (GNDANA), U$76.11 (GNDANA), U$76.14 (GNDANA), U$76.28 (GND), U$76.33 (GND_PAD), UFLANT.1 (GND), UFLANT.2 (GND), XOSCRF.2 (GND_2), XOSCRF.4 (GND_4)
unnamed: R6.2, RGBLED.3 (G)
unnamed: CN1.VBUS, FB2.1
unnamed: CN1.GND, FB1.1
unnamed: R7.2, RGBLED.4 (B)
unnamed: R4.2, RGBLED.2 (R)
unnamed: BTN.1, R1.1
PA06(R): R4.1, U$76.7 (PA06)
PA07(G): R6.1, U$76.8 (PA07)
PA08/I2C/SDA: ASWITCH.PIN6 (6), C20.1, U$76.9 (PA08)
PA09/I2C/SCL: ASWITCH.PIN4 (4), C19.2, U$76.10 (PA09)
PA14/XIN_MC/RX: U$76.15 (PA14)
PA15/XOUT_MC/TX: U$76.16 (PA15)
PA16/I2C: U$76.17 (PA16)
PA17/I2C: U$76.18 (PA17)
PA18/INTA: U$76.19 (PA18)
PA19/FSYNC: U$76.20 (PA19)
PA24/USBDM: CN1.D-, U$76.22 (PA24)
PA25/USBDP: CN1.D+, U$76.23 (PA25)
PA27(B): R7.1, U$76.25 (PA27)
PA28: U$76.27 (PA28)
PA30/SWCLK: U$1.P$4 (4), U$76.31 (PA30)
PA31/SWDIO: U$1.P$5 (5), U$76.32 (PA31)
RESET: C1.1, R1.2, R2.1, U$1.P$3 (3), U$76.26 (RESETN)
RFN: U$12.3, U$76.13 (RFN)
RFP: U$12.4, U$76.12 (RFP)
RFSWITCH_PIN1: ASWITCH.PIN1 (1), C24.1
RFSWITCH_PIN3: ASWITCH.PIN3 (3), C23.2
RFSWITCH_PIN5: ASWITCH.PIN5 (5), C18.2
VDDANA: C8.1, C22.2, L6.2, U$76.4 (VDDANA)
VDDCORE: C9.1, U$76.29 (VDDCORE)
VIN: C6.1, C7.1, FB2.2, LDO_VREG.VIN (3)
XTALIN: C14.2, U$76.2 (XTAL1), XOSCRF.1 (XTALIN)
XTALOUT: C15.1, U$76.1 (XTAL2), XOSCRF.3 (XTALOUT)

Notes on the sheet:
FemtoBeacon
1.0.0
ATMEL SAMR21E ARM CORTEX M0+
Released under MIT License (c) Femtoduino.com, 2015 by Alex Albino
(Power Snub)
(VDDIO)
(VDDIN)
